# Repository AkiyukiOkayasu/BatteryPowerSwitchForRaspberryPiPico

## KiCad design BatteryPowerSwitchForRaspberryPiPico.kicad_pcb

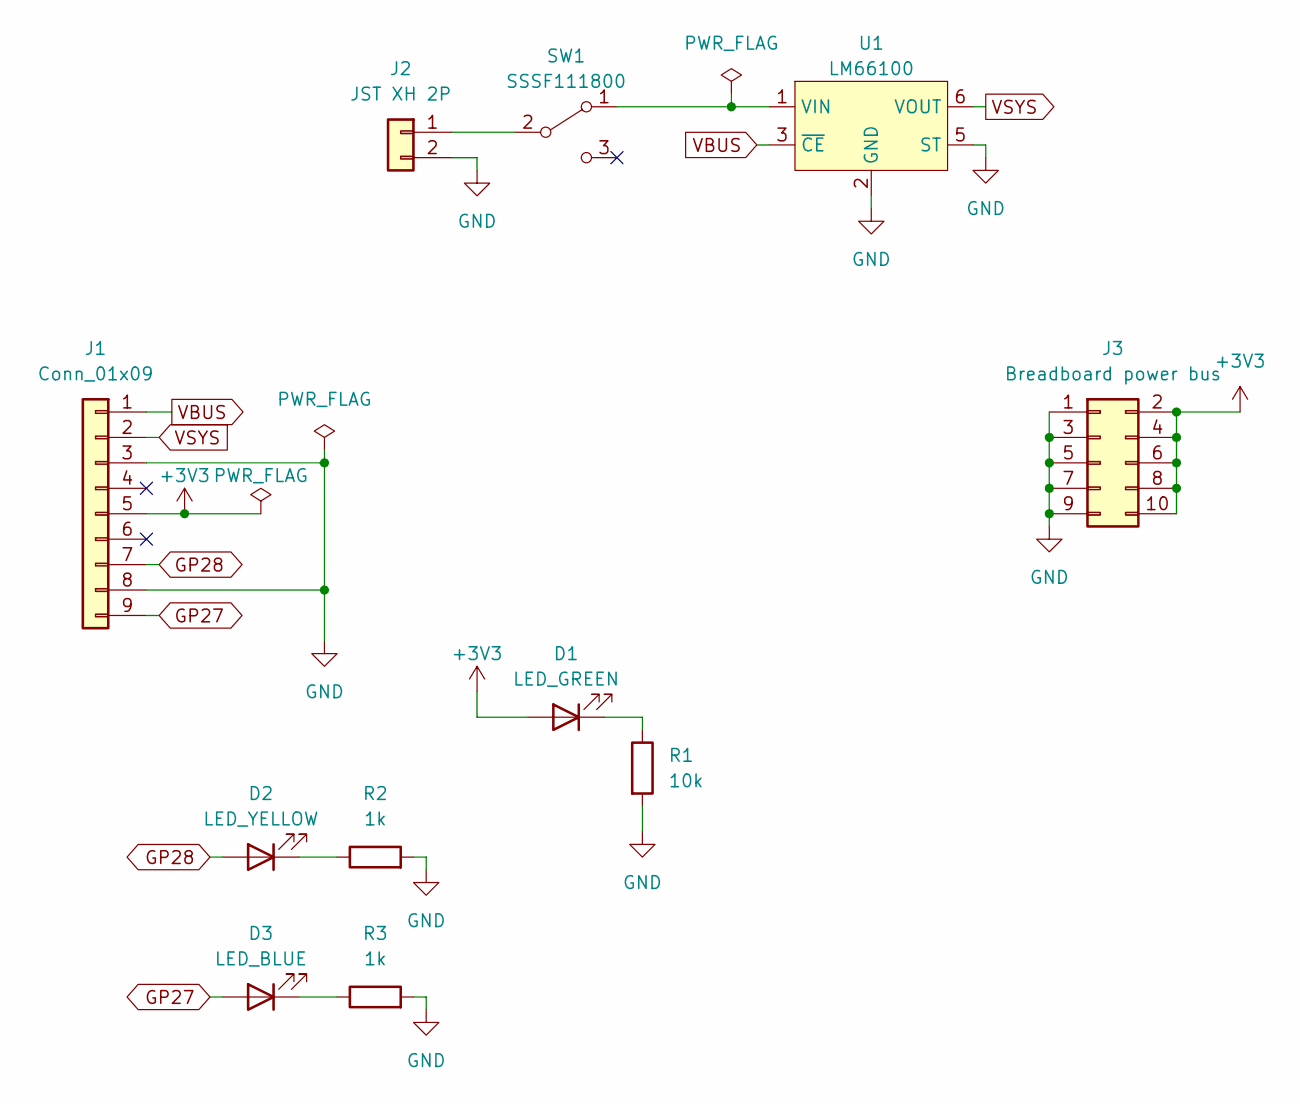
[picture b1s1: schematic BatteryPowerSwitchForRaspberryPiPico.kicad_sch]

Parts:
D1: LED_GREEN; LED_0603_1608Metric; LCSC C72043
D2: LED_YELLOW; LED_0603_1608Metric; LCSC C72038
D3: LED_BLUE; LED_0603_1608Metric; LCSC C72041
J1: Conn_01x09; PinHeader_1x09_P2.54mm_Vertical; LCSC C706881
J2: JST XH 2P; JST_XH_B2B-XH-A_1x02_P2.50mm_Vertical
J3: Breadboard power bus; PinHeader_2x05_P2.54mm_Vertical; LCSC C706895
R1: 10k; R_0603_1608Metric
R2, R3: 1k; R_0603_1608Metric
SW1: SSSF111800; ALPS_SSSF111800; LCSC C97450
U1: LM66100; SOT-363_SC-70-6_Handsoldering

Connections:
+3V3: D1.2 (A), J1.5, J3.2, J3.4, J3.6, J3.8, J3.10
GND: J1.3, J1.8, J2.2, J3.1, J3.3, J3.5, J3.7, J3.9, R1.2, R2.2, R3.2, U1.2 (GND), U1.5 (ST)
GP27: D3.2 (A), J1.9
GP28: D2.2 (A), J1.7
unnamed: D1.1 (K), R1.1
unnamed: D2.1 (K), R2.1
unnamed: D3.1 (K), R3.1
unnamed: J2.1, SW1.2 (B)
unnamed: SW1.1 (A), U1.1 (VIN)
VBUS: J1.1, U1.3 (~CE)
VSYS: J1.2, U1.6 (VOUT)

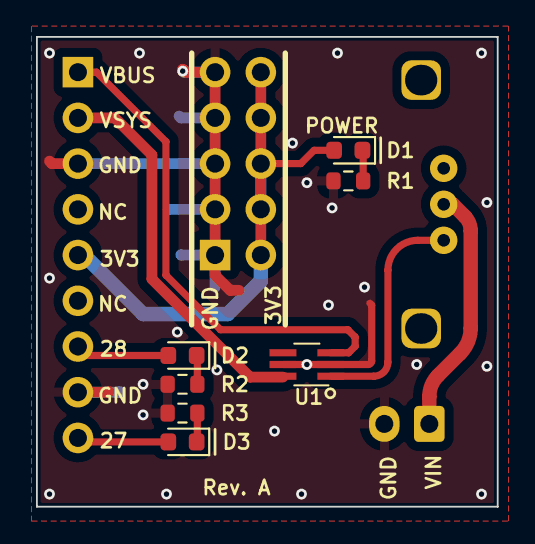
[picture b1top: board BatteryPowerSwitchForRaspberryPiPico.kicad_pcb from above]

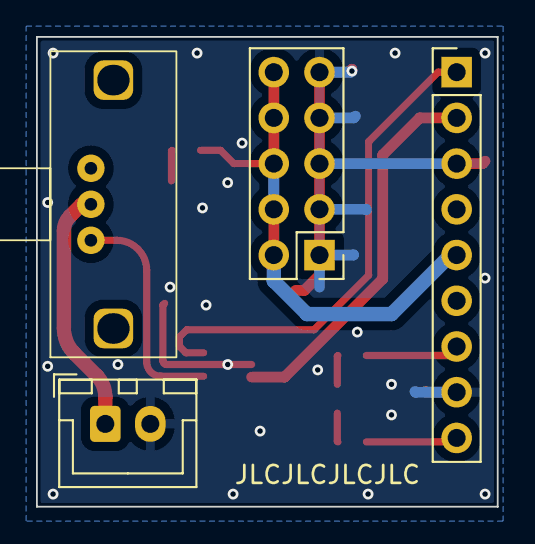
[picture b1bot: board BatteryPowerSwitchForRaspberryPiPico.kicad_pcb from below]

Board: 2 copper layers, 25.6 x 26.1 mm, 11 parts (4 on the bottom side), 11 nets.

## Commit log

2023-09-25 gitignore
